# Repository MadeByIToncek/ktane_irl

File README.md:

# KeepTalkingIRL

Remaking Keep Talking And Nobody Explodes ("KTANE") in real life with as little resources as possible while not
sacrificing gameplay.

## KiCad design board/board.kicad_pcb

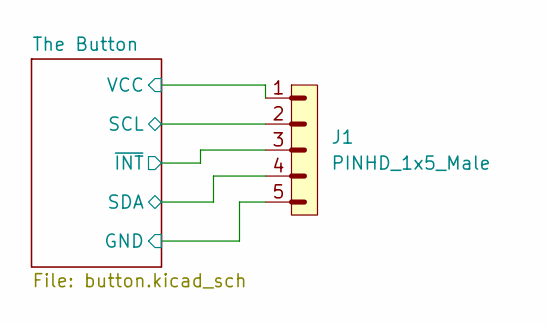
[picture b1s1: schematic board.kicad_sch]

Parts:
J1: PINHD_1x5_Male; PinHeader_1x05_P2.54mm_Horizontal

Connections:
/The Button/GND: J1.5; also elsewhere on the board
/The Button/SCL: J1.2; also elsewhere on the board
/The Button/SDA: J1.4; also elsewhere on the board
/The Button/VCC: J1.1; also elsewhere on the board
/The Button/~INT: J1.3; also elsewhere on the board

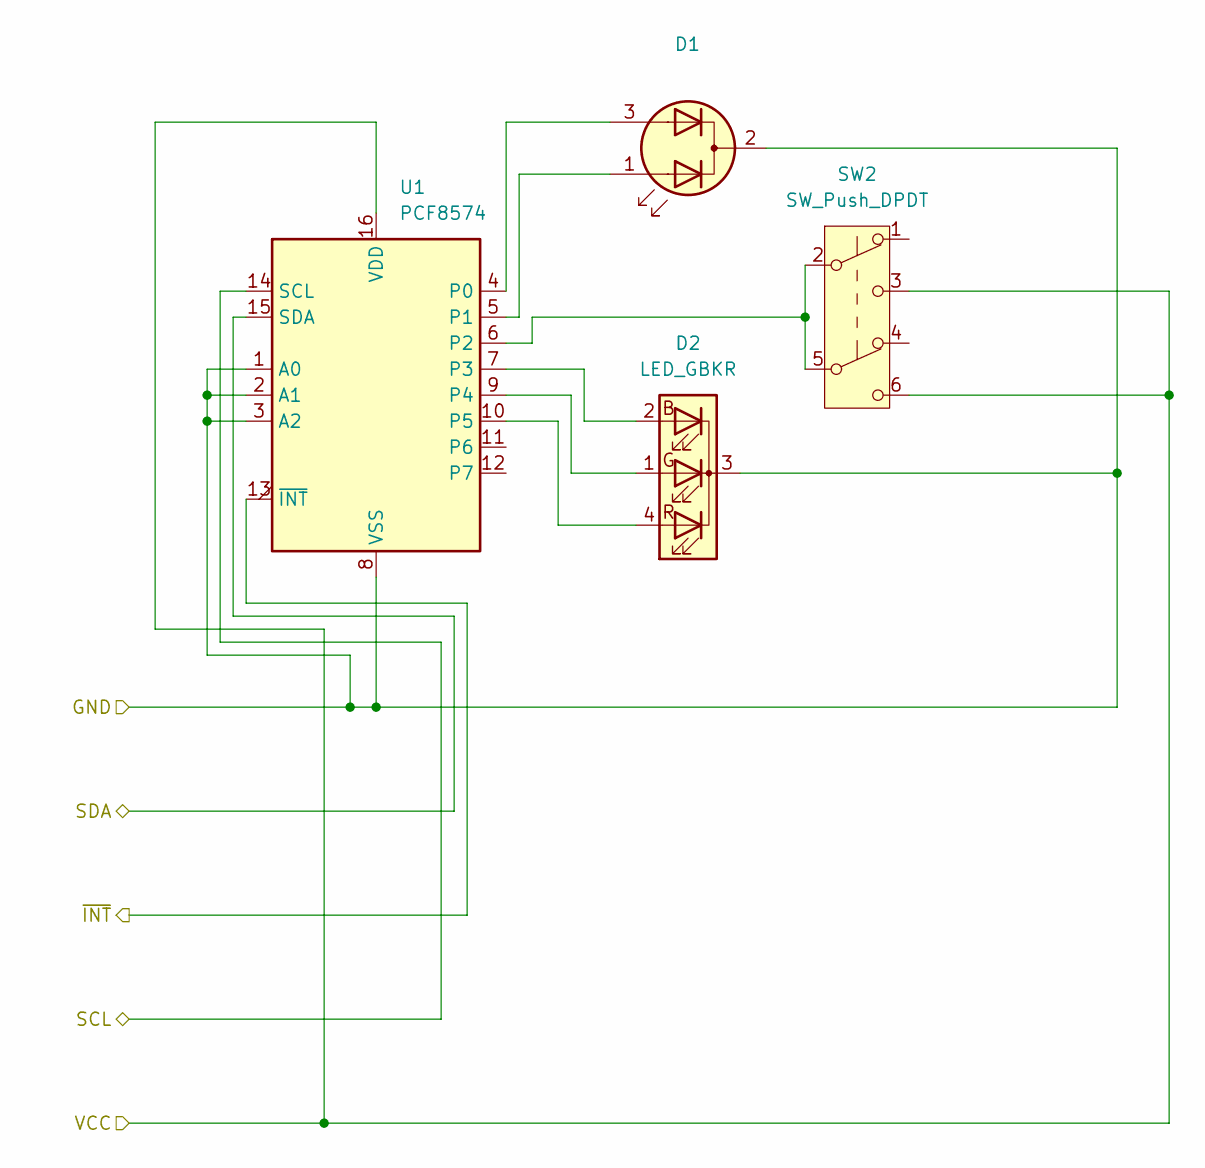
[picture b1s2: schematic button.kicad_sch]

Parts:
D1: LED_Dual_AKA; LED_D8.0mm-3
D2: LED_GBKR; LED_D5.0mm-4_RGB
SW2: SW_Push_DPDT; SW_Push_2P2T_Toggle_CK_PVA2xxH1xxxxxxV2
U1: PCF8574; SOIC-16W_7.5x10.3mm_P1.27mm

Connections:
/The Button/GND: D1.2 (K), D2.3 (K), U1.1 (A0), U1.2 (A1), U1.3 (A2), U1.8 (VSS); also elsewhere on the board
/The Button/SCL: U1.14 (SCL); also elsewhere on the board
/The Button/SDA: U1.15 (SDA); also elsewhere on the board
/The Button/VCC: SW2.3 (C), SW2.6 (C), U1.16 (VDD); also elsewhere on the board
/The Button/~INT: U1.13 (~INT); also elsewhere on the board
unnamed: D1.1 (A1), U1.5 (P1)
unnamed: D1.3 (A2), U1.4 (P0)
unnamed: D2.2 (BA), U1.7 (P3)
unnamed: D2.1 (GA), U1.9 (P4)
unnamed: D2.4 (RA), U1.10 (P5)
unnamed: SW2.2 (B), SW2.5 (B), U1.6 (P2)

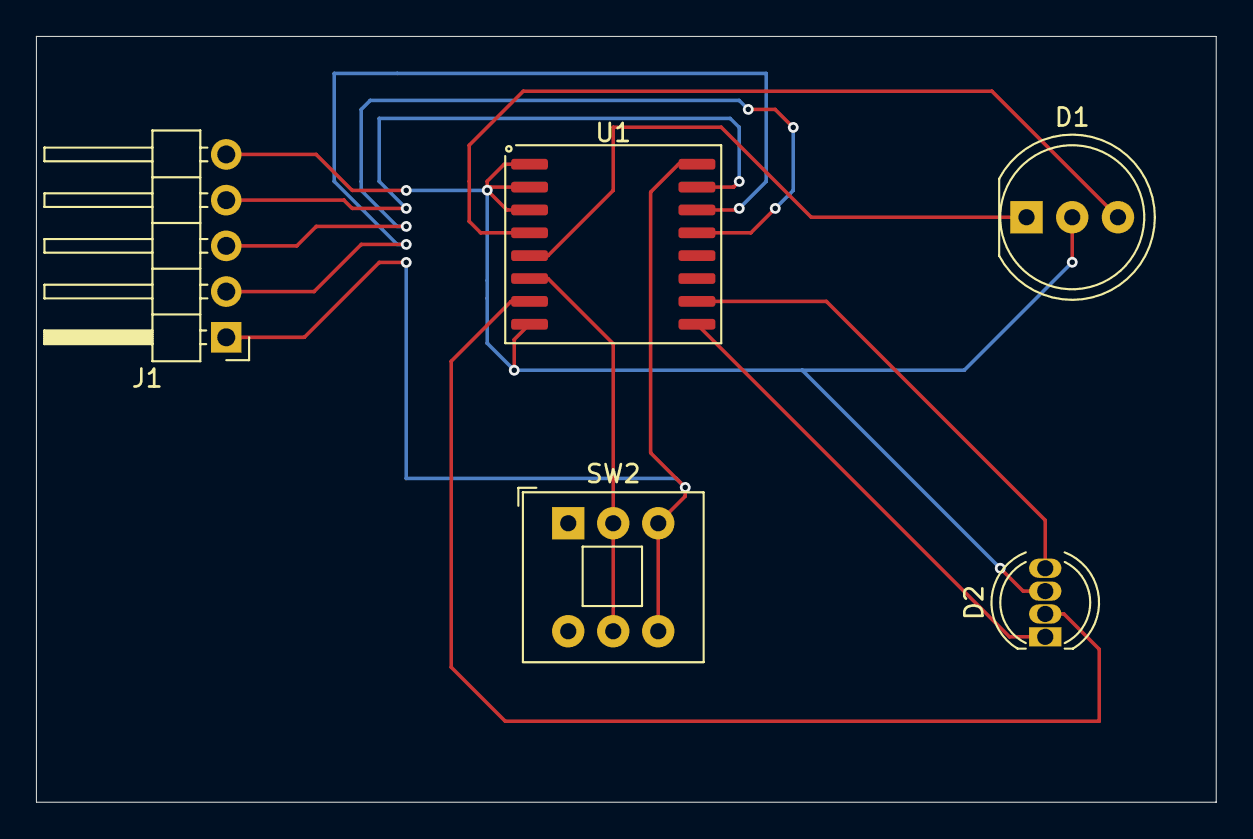
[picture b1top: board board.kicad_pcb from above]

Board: 2 copper layers, 65.5 x 42.5 mm, 5 parts (0 on the bottom side), 11 nets.

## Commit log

2024-05-21 Init
2024-05-21 Create LICENSE
2024-05-21 Adding 'THE BUTTON'
2024-05-21 Creating PCB for 'THE BUTTON'
2024-05-22 Adding some files to. gitignore
2024-05-22 Some KiCad work + gradle init
2024-05-22 Modifying README.md
2024-05-22 Adding README.md
2024-05-22 Init simple gradle project
2024-05-23 Moving to maven (possibly switching to C# later)
2024-05-23 Init C#
2024-05-23 Removing unnecessary files
2024-05-24 AOT experiments
2024-05-24 Some progress
2024-05-24 I2C library init
2024-05-25 Better UI work
2024-05-25 Copyright + Formatting
2024-05-26 Network init
2024-05-26 Log filtering
2024-05-26 License update
2024-05-26 Fixing typo in java files
2024-05-26 Config innit
2024-05-28 Adding i2c to i2c module for attiny
2024-05-28 Interrupter
2024-06-01 Update main.c
    Adding note that the code is not final.
2024-06-01 Adding CQL
2024-06-01 Create CI/CD workflow (#4)
    * Create makefile.yml
    * Delete .github/workflows/makefile.yml
    * Create maven.yml
    * Update maven.yml
    * Adding CQL
    * Update maven.yml
2024-06-01 Adding clean command to i2c2i2c module Makefile
2024-06-01 Adding status blink header library
2024-06-01 Trying to fix conflicts
2024-06-01 Editing coding style
2024-06-01 Setup progress
2024-06-01 Fixes #6
2024-06-01 Bump ch.qos.logback:logback-core from 1.4.14 to 1.5.6
    Bumps [ch.qos.logback:logback-core](https://github.com/qos-ch/logback) from 1.4.14 to 1.5.6.
    - [Commits](https://github.com/qos-ch/logback/compare/v_1.4.14...v_1.5.6)
    ---
    updated-dependencies:
    - dependency-name: ch.qos.logback:logback-core
    dependency-type: direct:production
2024-06-01 Bump ch.qos.logback:logback-classic from 1.4.14 to 1.5.6
    Bumps [ch.qos.logback:logback-classic](https://github.com/qos-ch/logback) from 1.4.14 to 1.5.6.
    - [Commits](https://github.com/qos-ch/logback/compare/v_1.4.14...v_1.5.6)
    ---
    updated-dependencies:
    - dependency-name: ch.qos.logback:logback-classic
    dependency-type: direct:production
2024-06-01 Bump org.apache.maven.plugins:maven-jar-plugin from 3.1.0 to 3.4.1
    Bumps [org.apache.maven.plugins:maven-jar-plugin](https://github.com/apache/maven-jar-plugin) from 3.1.0 to 3.4.1.
    - [Release notes](https://github.com/apache/maven-jar-plugin/releases)
    - [Commits](https://github.com/apache/maven-jar-plugin/compare/maven-jar-plugin-3.1.0...maven-jar-plugin-3.4.1)
    ---
    updated-dependencies:
    - dependency-name: org.apache.maven.plugins:maven-jar-plugin
2024-06-01 Docs?
2024-06-01 Adding docs branch to build
2024-06-01 Fixing cache
2024-06-01 Fixing build
2024-06-01 Reorganising CI running
2024-06-01 Docs (#15)
    * Docs?
    * Adding docs branch to build
    * Fixing cache
    * Fixing cache
    * Fixing cache
    * Fixing cache
2024-06-01 Fixing docs
2024-06-01 COC & CONTRIBUTING.md
2024-06-01 Bump org.apache.maven.plugins:maven-compiler-plugin from 3.8.1 to 3.13.0
    Bumps [org.apache.maven.plugins:maven-compiler-plugin](https://github.com/apache/maven-compiler-plugin) from 3.8.1 to 3.13.0.
    - [Release notes](https://github.com/apache/maven-compiler-plugin/releases)
    - [Commits](https://github.com/apache/maven-compiler-plugin/compare/maven-compiler-plugin-3.8.1...maven-compiler-plugin-3.13.0)
    ---
    updated-dependencies:
    - dependency-name: org.apache.maven.plugins:maven-compiler-plugin
2024-06-01 Bump org.apache.maven.plugins:maven-shade-plugin from 3.2.4 to 3.6.0
    Bumps [org.apache.maven.plugins:maven-shade-plugin](https://github.com/apache/maven-shade-plugin) from 3.2.4 to 3.6.0.
    - [Release notes](https://github.com/apache/maven-shade-plugin/releases)
    - [Commits](https://github.com/apache/maven-shade-plugin/compare/maven-shade-plugin-3.2.4...maven-shade-plugin-3.6.0)
    ---
    updated-dependencies:
    - dependency-name: org.apache.maven.plugins:maven-shade-plugin
2024-06-19 Bump ws in /docs in the npm_and_yarn group across 1 directory
    Bumps the npm_and_yarn group with 1 update in the /docs directory: [ws](https://github.com/websockets/ws).
    Updates `ws` from 7.5.9 to 7.5.10
    - [Release notes](https://github.com/websockets/ws/releases)
    - [Commits](https://github.com/websockets/ws/compare/7.5.9...7.5.10)
    ---
    updated-dependencies:
2024-06-24 Bump org.apache.maven.plugins:maven-jar-plugin from 3.4.1 to 3.4.2
    Bumps [org.apache.maven.plugins:maven-jar-plugin](https://github.com/apache/maven-jar-plugin) from 3.4.1 to 3.4.2.
    - [Release notes](https://github.com/apache/maven-jar-plugin/releases)
    - [Commits](https://github.com/apache/maven-jar-plugin/compare/maven-jar-plugin-3.4.1...maven-jar-plugin-3.4.2)
    ---
    updated-dependencies:
    - dependency-name: org.apache.maven.plugins:maven-jar-plugin
2024-07-04 Using rust instead of C in i2c2i2c
2024-07-05 Adding basic i2c library
2024-07-29 Bump pi4j.version from 2.6.0 to 2.6.1
    Bumps `pi4j.version` from 2.6.0 to 2.6.1.
    Updates `com.pi4j:pi4j-core` from 2.6.0 to 2.6.1
    - [Release notes](https://github.com/Pi4J/pi4j-v2/releases)
    - [Changelog](https://github.com/Pi4J/pi4j-v2/blob/develop/autoRelease)
    - [Commits](https://github.com/Pi4J/pi4j-v2/compare/2.6.0...2.6.1)
    Updates `com.pi4j:pi4j-plugin-raspberrypi` from 2.6.0 to 2.6.1
2024-08-12 Bump org.slf4j:slf4j-api from 2.0.13 to 2.0.16
    Bumps org.slf4j:slf4j-api from 2.0.13 to 2.0.16.
    ---
    updated-dependencies:
    - dependency-name: org.slf4j:slf4j-api
    dependency-type: direct:production
    update-type: version-update:semver-patch
2024-08-19 Bump ch.qos.logback:logback-classic from 1.5.6 to 1.5.7
    Bumps [ch.qos.logback:logback-classic](https://github.com/qos-ch/logback) from 1.5.6 to 1.5.7.
    - [Commits](https://github.com/qos-ch/logback/compare/v_1.5.6...v_1.5.7)
    ---
    updated-dependencies:
    - dependency-name: ch.qos.logback:logback-classic
    dependency-type: direct:production
2024-08-19 Bump ch.qos.logback:logback-core from 1.5.6 to 1.5.7
    Bumps [ch.qos.logback:logback-core](https://github.com/qos-ch/logback) from 1.5.6 to 1.5.7.
    - [Commits](https://github.com/qos-ch/logback/compare/v_1.5.6...v_1.5.7)
    ---
    updated-dependencies:
    - dependency-name: ch.qos.logback:logback-core
    dependency-type: direct:production
2024-08-31 Bump webpack in /docs in the npm_and_yarn group across 1 directory
    Bumps the npm_and_yarn group with 1 update in the /docs directory: [webpack](https://github.com/webpack/webpack).
    Updates `webpack` from 5.91.0 to 5.94.0
    - [Release notes](https://github.com/webpack/webpack/releases)
    - [Commits](https://github.com/webpack/webpack/compare/v5.91.0...v5.94.0)
    ---
    updated-dependencies:
2024-09-09 Bump ch.qos.logback:logback-classic from 1.5.6 to 1.5.8
    Bumps [ch.qos.logback:logback-classic](https://github.com/qos-ch/logback) from 1.5.6 to 1.5.8.
    - [Commits](https://github.com/qos-ch/logback/compare/v_1.5.6...v_1.5.8)
    ---
    updated-dependencies:
    - dependency-name: ch.qos.logback:logback-classic
    dependency-type: direct:production
2024-09-09 Bump ch.qos.logback:logback-core from 1.5.6 to 1.5.8
    Bumps [ch.qos.logback:logback-core](https://github.com/qos-ch/logback) from 1.5.6 to 1.5.8.
    - [Commits](https://github.com/qos-ch/logback/compare/v_1.5.6...v_1.5.8)
    ---
    updated-dependencies:
    - dependency-name: ch.qos.logback:logback-core
    dependency-type: direct:production
2024-09-30 Bump org.jetbrains:annotations from 24.1.0 to 25.0.0
    Bumps [org.jetbrains:annotations](https://github.com/JetBrains/java-annotations) from 24.1.0 to 25.0.0.
    - [Release notes](https://github.com/JetBrains/java-annotations/releases)
    - [Changelog](https://github.com/JetBrains/java-annotations/blob/master/CHANGELOG.md)
    - [Commits](https://github.com/JetBrains/java-annotations/compare/24.1.0...25.0.0)
    ---
    updated-dependencies:
2024-10-07 Bump pi4j.version from 2.6.1 to 2.7.0
    Bumps `pi4j.version` from 2.6.1 to 2.7.0.
    Updates `com.pi4j:pi4j-core` from 2.6.1 to 2.7.0
    - [Release notes](https://github.com/Pi4J/pi4j-v2/releases)
    - [Changelog](https://github.com/Pi4J/pi4j-v2/blob/develop/autoRelease)
    - [Commits](https://github.com/Pi4J/pi4j-v2/compare/2.6.1...2.7.0)
    Updates `com.pi4j:pi4j-plugin-raspberrypi` from 2.6.1 to 2.7.0
2024-10-14 Bump ch.qos.logback:logback-core from 1.5.6 to 1.5.10
    Bumps [ch.qos.logback:logback-core](https://github.com/qos-ch/logback) from 1.5.6 to 1.5.10.
    - [Commits](https://github.com/qos-ch/logback/compare/v_1.5.6...v_1.5.10)
    ---
    updated-dependencies:
    - dependency-name: ch.qos.logback:logback-core
    dependency-type: direct:production
2024-10-14 Bump ch.qos.logback:logback-classic from 1.5.6 to 1.5.10
    Bumps [ch.qos.logback:logback-classic](https://github.com/qos-ch/logback) from 1.5.6 to 1.5.10.
    - [Commits](https://github.com/qos-ch/logback/compare/v_1.5.6...v_1.5.10)
    ---
    updated-dependencies:
    - dependency-name: ch.qos.logback:logback-classic
    dependency-type: direct:production
2024-10-14 Bump org.jetbrains:annotations from 24.1.0 to 26.0.1
    Bumps [org.jetbrains:annotations](https://github.com/JetBrains/java-annotations) from 24.1.0 to 26.0.1.
    - [Release notes](https://github.com/JetBrains/java-annotations/releases)
    - [Changelog](https://github.com/JetBrains/java-annotations/blob/master/CHANGELOG.md)
    - [Commits](https://github.com/JetBrains/java-annotations/compare/24.1.0...26.0.1)
    ---
    updated-dependencies:
2024-10-21 Bump ch.qos.logback:logback-core from 1.5.6 to 1.5.11
    Bumps [ch.qos.logback:logback-core](https://github.com/qos-ch/logback) from 1.5.6 to 1.5.11.
    - [Commits](https://github.com/qos-ch/logback/compare/v_1.5.6...v_1.5.11)
    ---
    updated-dependencies:
    - dependency-name: ch.qos.logback:logback-core
    dependency-type: direct:production
2024-10-21 Bump ch.qos.logback:logback-classic from 1.5.6 to 1.5.11
    Bumps [ch.qos.logback:logback-classic](https://github.com/qos-ch/logback) from 1.5.6 to 1.5.11.
    - [Commits](https://github.com/qos-ch/logback/compare/v_1.5.6...v_1.5.11)
    ---
    updated-dependencies:
    - dependency-name: ch.qos.logback:logback-classic
    dependency-type: direct:production
2024-10-28 Bump ch.qos.logback:logback-core from 1.5.6 to 1.5.12
    Bumps [ch.qos.logback:logback-core](https://github.com/qos-ch/logback) from 1.5.6 to 1.5.12.
    - [Commits](https://github.com/qos-ch/logback/compare/v_1.5.6...v_1.5.12)
    ---
    updated-dependencies:
    - dependency-name: ch.qos.logback:logback-core
    dependency-type: direct:production
2024-10-28 Bump ch.qos.logback:logback-classic from 1.5.6 to 1.5.12
    Bumps [ch.qos.logback:logback-classic](https://github.com/qos-ch/logback) from 1.5.6 to 1.5.12.
    - [Commits](https://github.com/qos-ch/logback/compare/v_1.5.6...v_1.5.12)
    ---
    updated-dependencies:
    - dependency-name: ch.qos.logback:logback-classic
    dependency-type: direct:production
